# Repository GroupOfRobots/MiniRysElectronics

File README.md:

# RyśBoard Hardware Controller

This project involves the design and development of the RyśBoard hardware controller, a custom PCB created to manage a robotic system. The project aims to enhance the performance of the previous controller and involves various stages such as component selection, PCB manufacturing, and assembly. The documentation outlines the key sections of the controller, its power sources, communication interfaces, and overall production process.

## Table of Contents

1. [Key Sections of the Controller](#key-sections-of-the-controller)
   - [24V Power Supply](#24v-power-supply)
   - [5V Power Supply](#5v-power-supply)
   - [Motor Drivers](#motor-drivers)
   - [Battery Voltage Monitoring](#battery-voltage-monitoring)
   - [Battery Connectors](#battery-connectors)
   - [I/O Connectors](#io-connectors)
   - [Configurable Indicators](#configurable-indicators)
   - [Mounting Options](#mounting-options)
3. [Production Process](#production-process)
   - [Initial Project Design](#initial-project-design)
   - [Final Design in KiCad](#final-design-in-kicad)
   - [PCB Assembly](#pcb-assembly)

---

## Project Overview

This report summarizes the development of the RyśBoard hardware controller, which underwent several updates to improve its functionality. The work involved ordering components, manufacturing and assembling the PCBs, and evaluating the performance of the power supply systems.

---

## Key Sections of the Controller

### 24V Power Supply

The 24V power supply is based on the LM51231-Q1 chip and provides up to 2.5A, delivering max 60W of power. This ensures sufficient power for the stepper motors and their drivers, with a margin to accommodate future increases in power requirements.

### 5V Power Supply

A TPS565242-based 5V power supply provides up to 4A, delivering max 20W of power. It is designed to power the Raspberry Pi 4 and Raspberry Pi 5, allowing for smooth operation even with additional accessories such as fans.

### Motor Drivers

The motor drivers use L6470H chips, which meet the requirements of the stepper motors (drawing up to 1A per driver under full load). These drivers are essential for stabilizing motor control.

### Battery Voltage Monitoring

The MAX11613 ADC monitors the voltage of three batteries, each connected to a separate channel. This information is communicated to the control unit via an I²C bus, allowing real-time monitoring of battery status.

### Battery Connectors

Three battery connectors are currently used, but due to their large size, there may be a future revision to consolidate them into a single, more compact connector to optimize space on the PCB.

### I/O Connectors

The board includes dedicated connectors for each stepper motor, eight connectors for I²C sensors, and one connector each for SPI and UART devices. A 5V fan connector is also available for cooling.

### Configurable Indicators

The board is equipped with configurable LEDs (red and green) connected to GPIO pins 23 and 24 on the control unit. These can be used to signal different status conditions.

### Mounting Options

The controller is compatible with the Raspberry Pi HAT standard, allowing easy integration with Raspberry Pi systems. Care has been taken to ensure electrical insulation and secure mounting.

---

## Production Process

### Initial Project Design

The initial design phase involved five key tasks:
1. Designing the HAT-compliant add-on board for Raspberry Pi.
2. Proper placement of components for the 24V and 5V power supplies.
3. Ensuring effective heat dissipation for the motor drivers.
4. Positioning passive components for ADC and other peripherals.
5. Routing power and signal paths.

### Final Design in KiCad

The KiCad design process was iterative, focusing on:
- Component placement to ensure efficient routing.
- Optimizing power trace lengths and widths for lower heat generation and energy loss.
- Optimizing signal trace lengths and placement for lower crosstalk.
- Revising the transistor selection for the 24V power supply to improve efficiency and component availability.

Final modifications included changing the location of key components for better thermal management and adding identification markings for easier assembly.

### PCB Assembly

The assembly phase involved:
1. Ordering components primarily from Mouser Electronics.
2. Soldering the components onto the PCB.
3. Inspecting the board for any mechanical defects, such as excess solder or improper connections.

The PCB assembly required soldering both the top and bottom components, with careful attention to ensure proper connections and functionality.

---

## Project Status

- **Current version**: Final (PCB ver. 1.1)
- **Changes since last iteration**: Fixed problems with stability of internal voltage regulators of L6470H drivers

---

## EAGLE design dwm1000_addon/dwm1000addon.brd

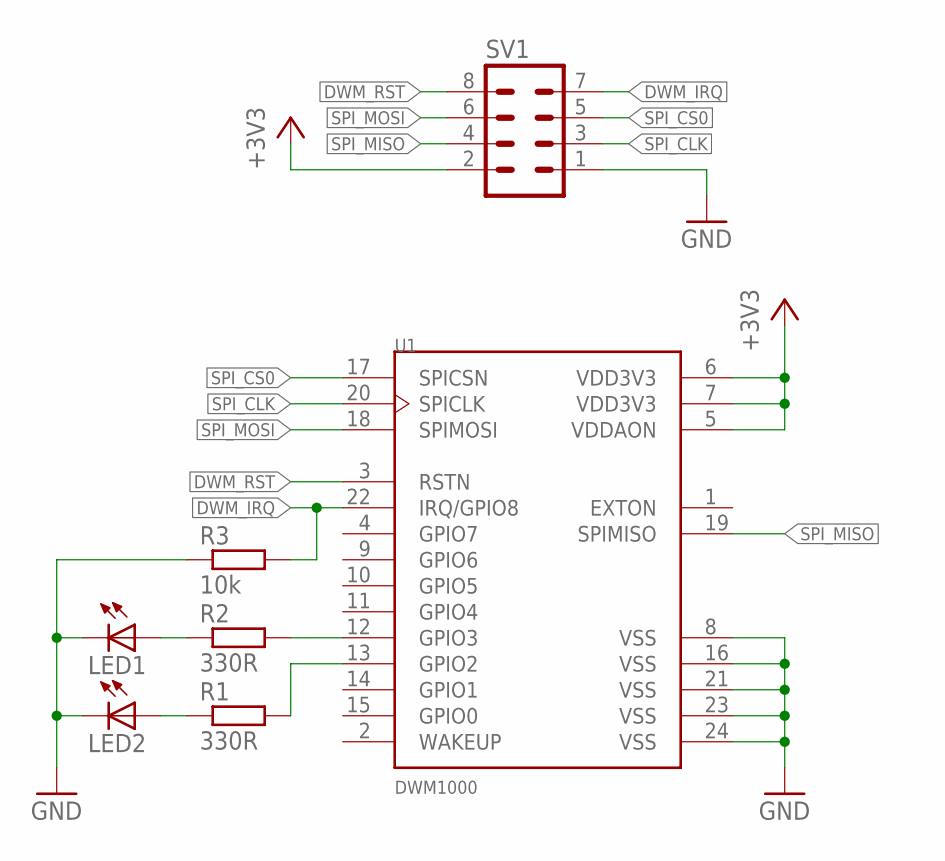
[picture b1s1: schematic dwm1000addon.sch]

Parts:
LED1, LED2: LEDCHIPLED_0603; CHIPLED_0603
R1, R2: 330R; R0603
R3: 10k; R0603
SV1: MA04-2
U1: DWM1000; XCVR_DWM1000

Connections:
+3V3: SV1.2, U1.5 (VDDAON), U1.6 (VDD3V3), U1.7 (VDD3V3)
DWM_IRQ: R3.2, SV1.7, U1.22 (IRQ/GPIO8)
DWM_RST: SV1.8, U1.3 (RSTN)
GND: LED1.C, LED2.C, R3.1, SV1.1, U1.8 (VSS), U1.16 (VSS), U1.21 (VSS), U1.23 (VSS), U1.24 (VSS)
unnamed: LED2.A, R1.1
unnamed: R1.2, U1.13 (GPIO2)
unnamed: R2.2, U1.12 (GPIO3)
unnamed: LED1.A, R2.1
SPI_CLK: SV1.3, U1.20 (SPICLK)
SPI_CS0: SV1.5, U1.17 (SPICSN)
SPI_MISO: SV1.4, U1.19 (SPIMISO)
SPI_MOSI: SV1.6, U1.18 (SPIMOSI)

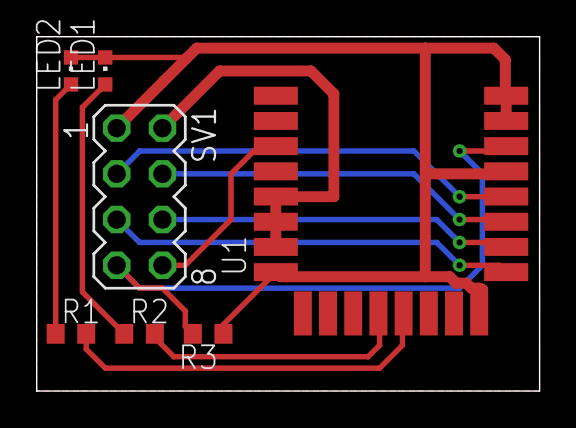
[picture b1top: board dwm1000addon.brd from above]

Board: 2 copper layers, 27.9 x 19.7 mm, 7 parts (0 on the bottom side), 12 nets.

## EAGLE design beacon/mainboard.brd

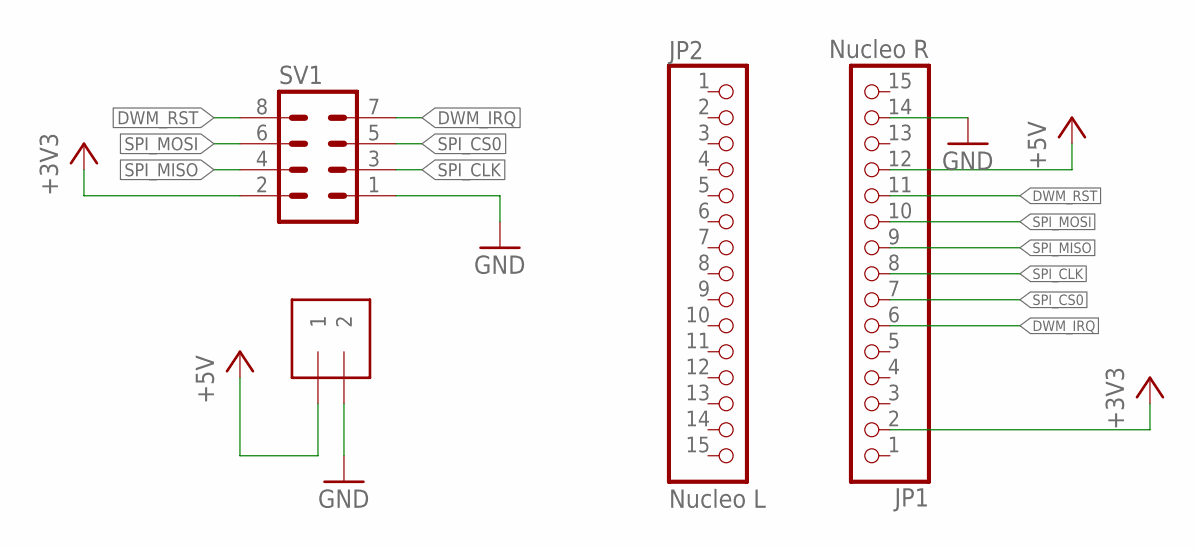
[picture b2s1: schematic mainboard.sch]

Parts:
J1: 1X2-3.5MM
JP1: Nucleo R; 1X15
JP2: Nucleo L; 1X15
SV1: MA04-2

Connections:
+3V3: JP1.2, SV1.2
+5V: J1.1, JP1.12
DWM_IRQ: JP1.6, SV1.7
DWM_RST: JP1.11, SV1.8
GND: J1.2, JP1.14, SV1.1
SPI_CLK: JP1.8, SV1.3
SPI_CS0: JP1.7, SV1.5
SPI_MISO: JP1.9, SV1.4
SPI_MOSI: JP1.10, SV1.6

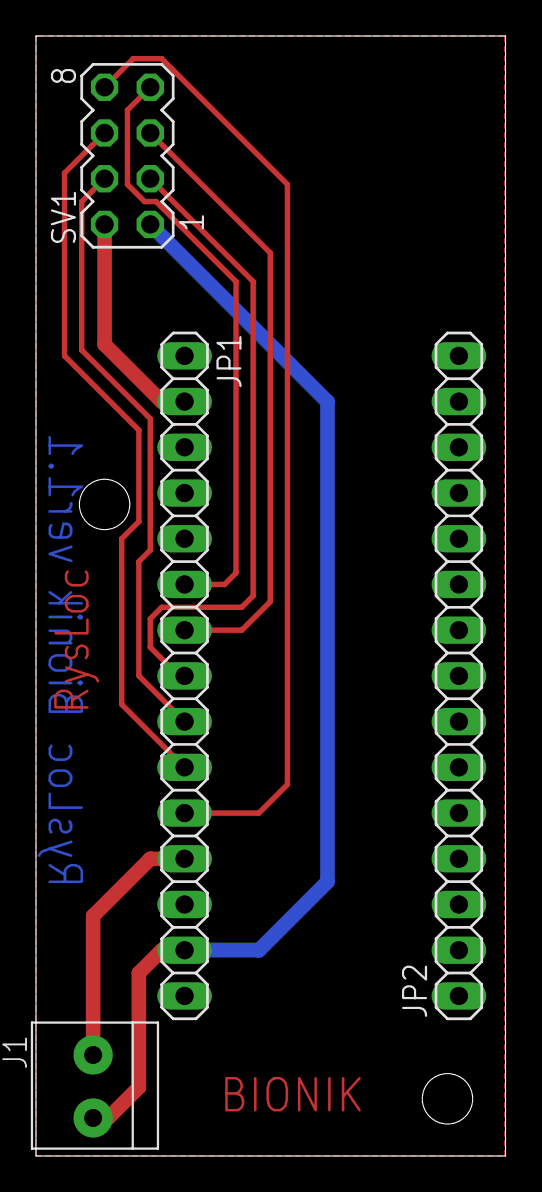
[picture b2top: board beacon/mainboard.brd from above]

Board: 2 copper layers, 26.1 x 62.2 mm, 4 parts (0 on the bottom side), 9 nets.

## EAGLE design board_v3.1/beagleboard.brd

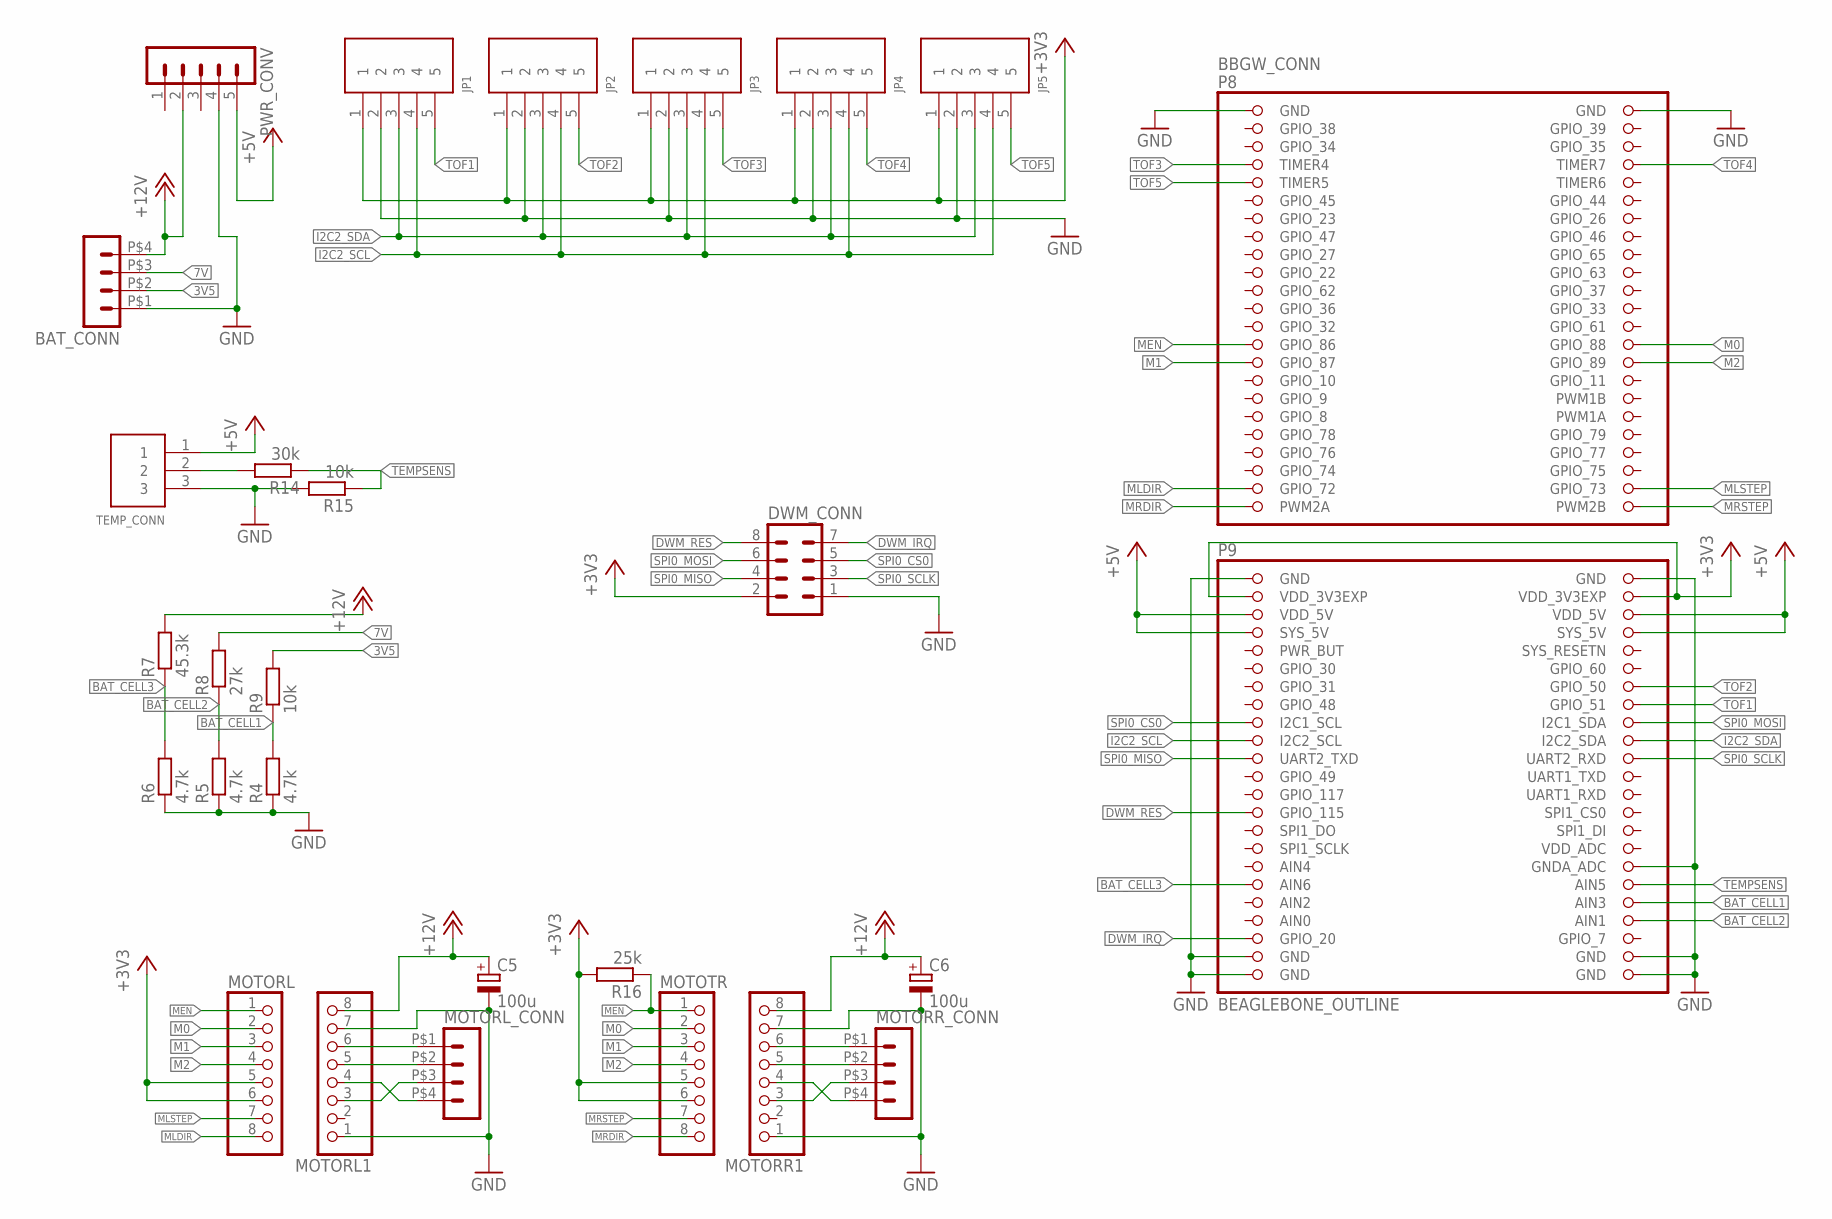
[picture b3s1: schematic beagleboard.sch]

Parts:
BAT_CONN: HEADER_POS4_43045-0412; 43045-0412
BBGW_CONN: BEAGLEBONE_OUTLINE; BEAGLEBONE_SHIELD
C5, C6: 100u; 153CLV-0405
DWM_CONN: MA04-2
JP1, JP2, JP3, JP4, JP5: 5PIN; B5B-PH-K-S
MOTORL, MOTORL1: PINHD-1X8; 1X08
MOTORL_CONN: HEADER_POS4_43045-0412; 43045-0412
MOTORR1: PINHD-1X8; 1X08
MOTORR_CONN: HEADER_POS4_43045-0412; 43045-0412
MOTOTR: PINHD-1X8; 1X08
PWR_CONV: MA05-1
R4, R5, R6: 4.7k; R0603
R7: 45.3k; R0603
R8: 27k; R0603
R9, R15: 10k; R0603
R14: 30k; R0603
R16: 25k; R0805
TEMP_CONN: 3PIN; B3B-PH-K-S

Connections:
3V5: BAT_CONN.P$2 (2), R9.2
7V: BAT_CONN.P$3 (3), R8.2
+3V3: BBGW_CONN.49 (VDD_3V3EXP), BBGW_CONN.50 (VDD_3V3EXP), DWM_CONN.2, JP1.1, JP2.1, JP3.1, JP4.1, JP5.1, MOTORL.5, MOTORL.6, MOTOTR.5, MOTOTR.6, R16.2
+5V: BBGW_CONN.51 (VDD_5V), BBGW_CONN.52 (VDD_5V), BBGW_CONN.53 (SYS_5V), BBGW_CONN.54 (SYS_5V), PWR_CONV.5, TEMP_CONN.1
+12V: BAT_CONN.P$4 (4), C5.+, C6.+, MOTORL1.8, MOTORR1.8, PWR_CONV.2, R7.2
AIN0: BBGW_CONN.85 (AIN0)
BAT_CELL1: BBGW_CONN.84 (AIN3), R4.2, R9.1
BAT_CELL2: BBGW_CONN.86 (AIN1), R5.2, R8.1
BAT_CELL3: BBGW_CONN.81 (AIN6), R6.2, R7.1
DWM_IRQ: BBGW_CONN.87 (GPIO_20), DWM_CONN.7
DWM_RES: BBGW_CONN.73 (GPIO_115), DWM_CONN.8
GND: BAT_CONN.P$1 (1), BBGW_CONN.1 (GND), BBGW_CONN.2 (GND), BBGW_CONN.47 (GND), BBGW_CONN.48 (GND), BBGW_CONN.80 (GNDA_ADC), BBGW_CONN.89 (GND), BBGW_CONN.90 (GND), BBGW_CONN.91 (GND), BBGW_CONN.92 (GND), C5.-, C6.-, DWM_CONN.1, JP1.2, JP2.2, JP3.2, JP4.2, JP5.2, MOTORL1.1, MOTORL1.7, MOTORR1.1, MOTORR1.7, PWR_CONV.4, R4.1, R5.1, R6.1, R15.2, TEMP_CONN.3
I2C2_SCL: BBGW_CONN.65 (I2C2_SCL), JP1.4, JP2.4, JP3.4, JP4.4, JP5.4
I2C2_SDA: BBGW_CONN.66 (I2C2_SDA), JP1.3, JP2.3, JP3.3, JP4.3, JP5.3
M0: BBGW_CONN.28 (GPIO_88), MOTORL.2, MOTOTR.2
M1: BBGW_CONN.29 (GPIO_87), MOTORL.3, MOTOTR.3
M2: BBGW_CONN.30 (GPIO_89), MOTORL.4, MOTOTR.4
MEN: BBGW_CONN.27 (GPIO_86), MOTORL.1, MOTOTR.1, R16.1
MLDIR: BBGW_CONN.43 (GPIO_72), MOTORL.8
MLSTEP: BBGW_CONN.44 (GPIO_73), MOTORL.7
MRDIR: BBGW_CONN.45 (PWM2A), MOTOTR.8
MRSTEP: BBGW_CONN.46 (PWM2B), MOTOTR.7
unnamed: MOTORL1.3, MOTORL_CONN.P$3 (3)
unnamed: MOTORL1.4, MOTORL_CONN.P$4 (4)
unnamed: MOTORR1.3, MOTORR_CONN.P$3 (3)
unnamed: MOTORR1.4, MOTORR_CONN.P$4 (4)
unnamed: MOTORL1.6, MOTORL_CONN.P$1 (1)
unnamed: MOTORL1.5, MOTORL_CONN.P$2 (2)
unnamed: MOTORR1.6, MOTORR_CONN.P$1 (1)
unnamed: MOTORR1.5, MOTORR_CONN.P$2 (2)
unnamed: R14.2, TEMP_CONN.2
SPI0_CS0: BBGW_CONN.63 (I2C1_SCL), DWM_CONN.5
SPI0_MISO: BBGW_CONN.67 (UART2_TXD), DWM_CONN.4
SPI0_MOSI: BBGW_CONN.64 (I2C1_SDA), DWM_CONN.6
SPI0_SCLK: BBGW_CONN.68 (UART2_RXD), DWM_CONN.3
TEMPSENS: BBGW_CONN.82 (AIN5), R14.1, R15.1
TOF1: BBGW_CONN.62 (GPIO_51), JP1.5
TOF2: BBGW_CONN.60 (GPIO_50), JP2.5
TOF3: BBGW_CONN.7 (TIMER4), JP3.5
TOF4: BBGW_CONN.8 (TIMER7), JP4.5
TOF5: BBGW_CONN.9 (TIMER5), JP5.5

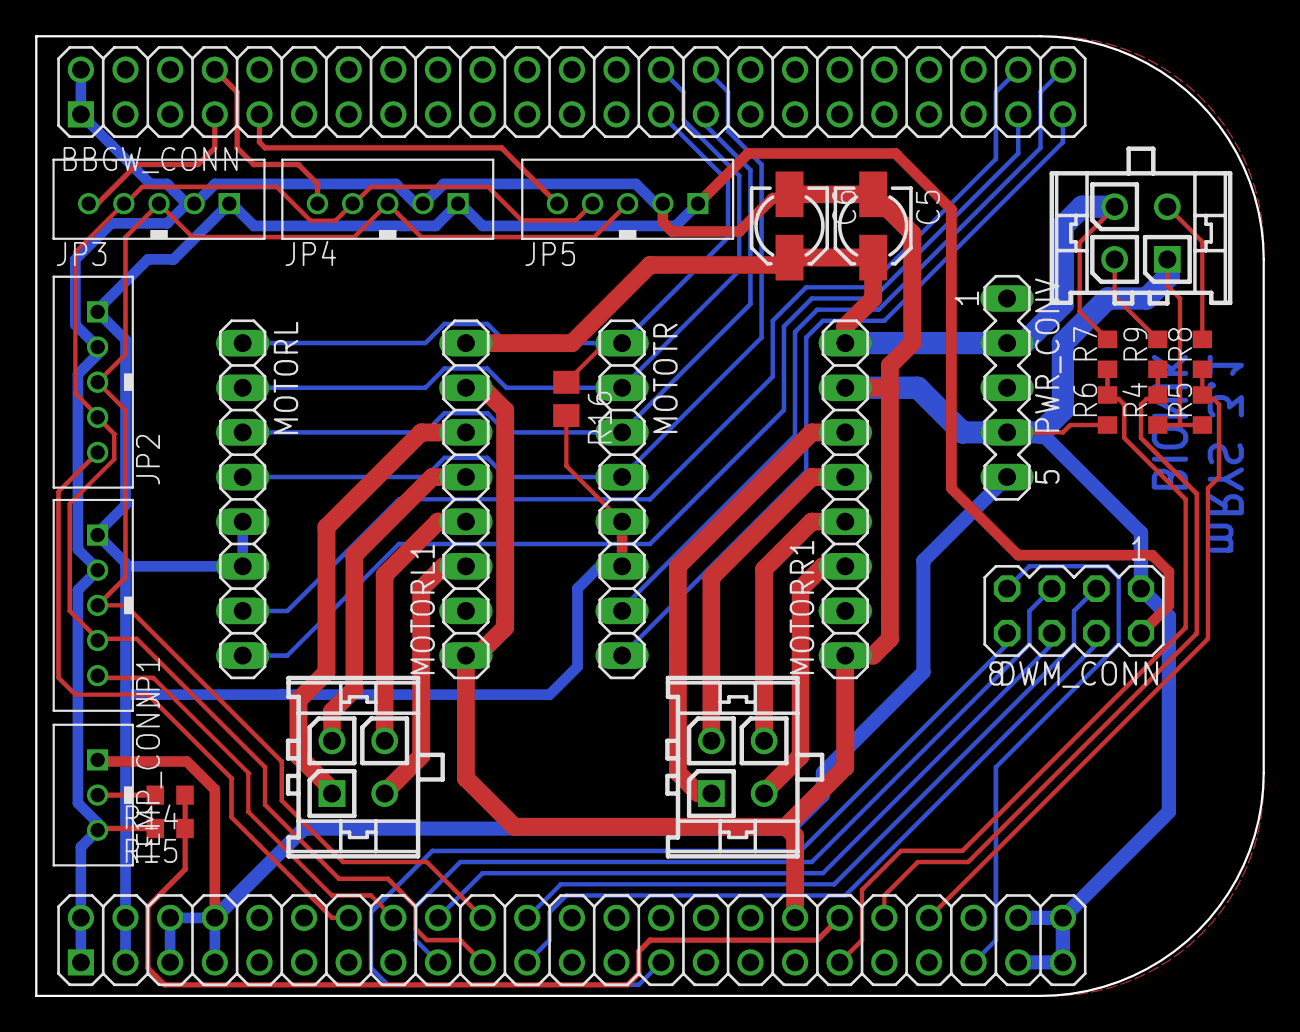
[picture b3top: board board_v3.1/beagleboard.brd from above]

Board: 2 copper layers, 69.8 x 54.6 mm, 27 parts (0 on the bottom side), 40 nets.

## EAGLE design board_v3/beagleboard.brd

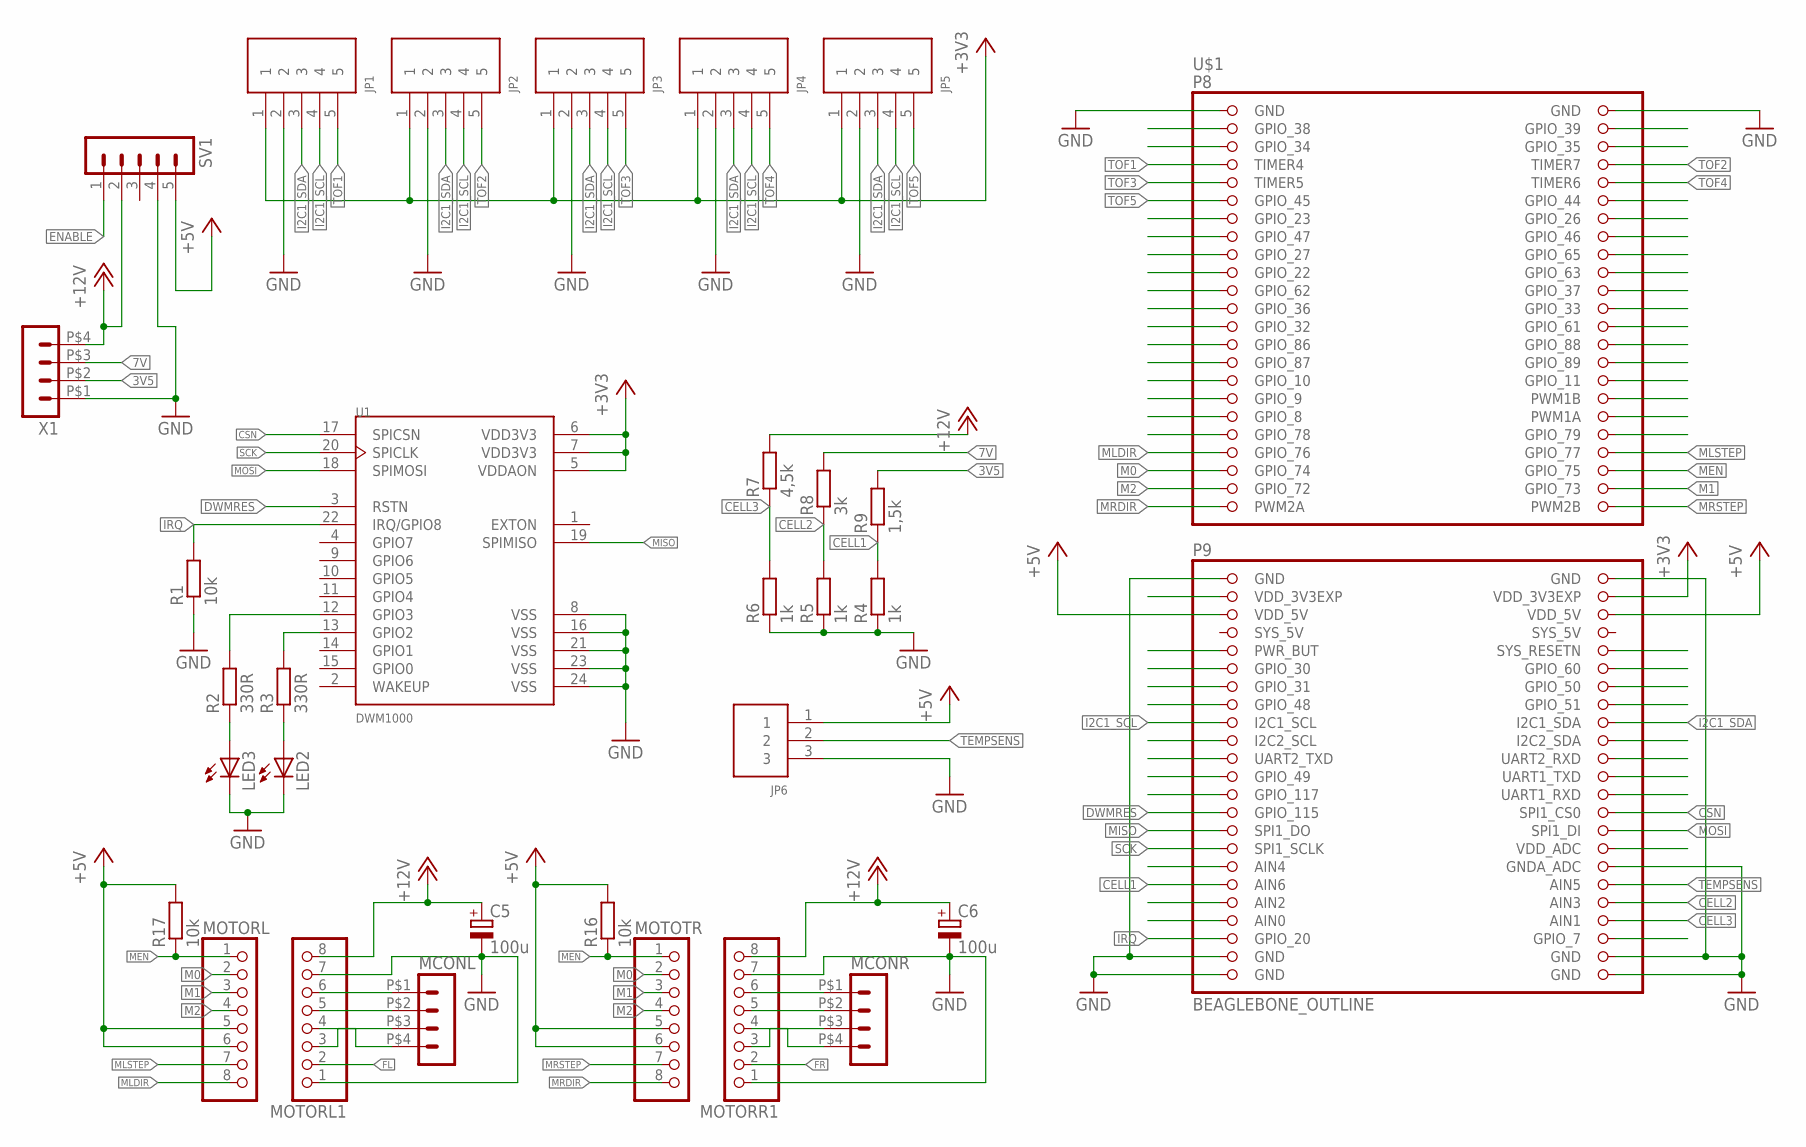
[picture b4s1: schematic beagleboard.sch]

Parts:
C5, C6: 100u; 153CLV-0405
JP1, JP2, JP3, JP4, JP5: 5PIN; B5B-PH-K-S
JP6: 3PIN; B3B-PH-K-S
LED2, LED3: LEDSML0603; SML0603
MCONL: HEADER_POS4_43045-0412; 43045-0412
MCONR: HEADER_POS4_43045-0412; 43045-0412
MOTORL, MOTORL1: PINHD-1X8; 1X08
MOTORR1: PINHD-1X8; 1X08
MOTOTR: PINHD-1X8; 1X08
R1: 10k; R0603
R2, R3: 330R; R0603
R4, R5, R6: 1k; R0603
R7: 4,5k; R0603
R8: 3k; R0603
R9: 1,5k; R0603
R16, R17: 10k; R0805
SV1: MA05-1
U1: DWM1000; XCVR_DWM1000
U$1: BEAGLEBONE_OUTLINE; BEAGLEBONE_SHIELD
X1: HEADER_POS4_43045-0412; 43045-0412

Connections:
3V5: R9.2, X1.P$2 (2)
7V: R8.2, X1.P$3 (3)
+3V3: JP1.1, JP2.1, JP3.1, JP4.1, JP5.1, U1.5 (VDDAON), U1.6 (VDD3V3), U1.7 (VDD3V3), U$1.50 (VDD_3V3EXP)
+5V: JP6.1, MOTORL.5, MOTORL.6, MOTOTR.5, MOTOTR.6, R16.2, R17.2, SV1.5, U$1.51 (VDD_5V), U$1.52 (VDD_5V)
+12V: C5.+, C6.+, MOTORL1.8, MOTORR1.8, R7.2, SV1.2, X1.P$4 (4)
CELL1: R4.2, R9.1, U$1.81 (AIN6)
CELL2: R5.2, R8.1, U$1.84 (AIN3)
CELL3: R6.2, R7.1, U$1.86 (AIN1)
CSN: U1.17 (SPICSN), U$1.74 (SPI1_CS0)
D4ECHO: U$1.85 (AIN0)
D4TRIG: U$1.83 (AIN2)
DWMRES: U1.3 (RSTN), U$1.73 (GPIO_115)
ENABLE: SV1.1
FL: MOTORL1.2
FR: MOTORR1.2
GND: C5.-, C6.-, JP1.2, JP2.2, JP3.2, JP4.2, JP5.2, JP6.3, LED2.C, LED3.C, MOTORL1.1, MOTORL1.7, MOTORR1.1, MOTORR1.7, R1.1, R4.1, R5.1, R6.1, SV1.4, U1.8 (VSS), U1.16 (VSS), U1.21 (VSS), U1.23 (VSS), U1.24 (VSS), U$1.1 (GND), U$1.2 (GND), U$1.47 (GND), U$1.80 (GNDA_ADC), U$1.89 (GND), U$1.90 (GND), U$1.91 (GND), U$1.92 (GND), X1.P$1 (1)
I2C1_SCL: JP1.4, JP2.4, JP3.4, JP4.4, JP5.4, U$1.63 (I2C1_SCL)
I2C1_SDA: JP1.3, JP2.3, JP3.3, JP4.3, JP5.3, U$1.64 (I2C1_SDA)
IRQ: R1.2, U1.22 (IRQ/GPIO8), U$1.87 (GPIO_20)
M0: MOTORL.2, MOTOTR.2, U$1.41 (GPIO_74)
M1: MOTORL.3, MOTOTR.3, U$1.44 (GPIO_73)
M2: MOTORL.4, MOTOTR.4, U$1.43 (GPIO_72)
MEN: MOTORL.1, MOTOTR.1, R16.1, R17.1, U$1.42 (GPIO_75)
MISO: U1.19 (SPIMISO), U$1.75 (SPI1_DO)
MLDIR: MOTORL.8, U$1.39 (GPIO_76)
MLSTEP: MOTORL.7, U$1.40 (GPIO_77)
MOSI: U1.18 (SPIMOSI), U$1.76 (SPI1_DI)
MRDIR: MOTOTR.8, U$1.45 (PWM2A)
MRSTEP: MOTOTR.7, U$1.46 (PWM2B)
unnamed: MCONL.P$4 (4), MOTORL1.4
unnamed: R3.2, U1.13 (GPIO2)
unnamed: R2.2, U1.12 (GPIO3)
unnamed: LED2.A, R3.1
unnamed: LED3.A, R2.1
unnamed: MCONL.P$1 (1), MOTORL1.6
unnamed: MCONL.P$2 (2), MOTORL1.5
unnamed: MCONL.P$3 (3), MOTORL1.3
unnamed: MCONR.P$1 (1), MOTORR1.6
unnamed: MCONR.P$2 (2), MOTORR1.5
unnamed: MCONR.P$4 (4), MOTORR1.4
unnamed: MCONR.P$3 (3), MOTORR1.3
SCK: U1.20 (SPICLK), U$1.77 (SPI1_SCLK)
SYS_5V: U$1.53 (SYS_5V)
TEMPSENS: JP6.2, U$1.82 (AIN5)
TOF1: JP1.5, U$1.7 (TIMER4)
TOF2: JP2.5, U$1.8 (TIMER7)
TOF3: JP3.5, U$1.9 (TIMER5)
TOF4: JP4.5, U$1.10 (TIMER6)
TOF5: JP5.5, U$1.11 (GPIO_45)

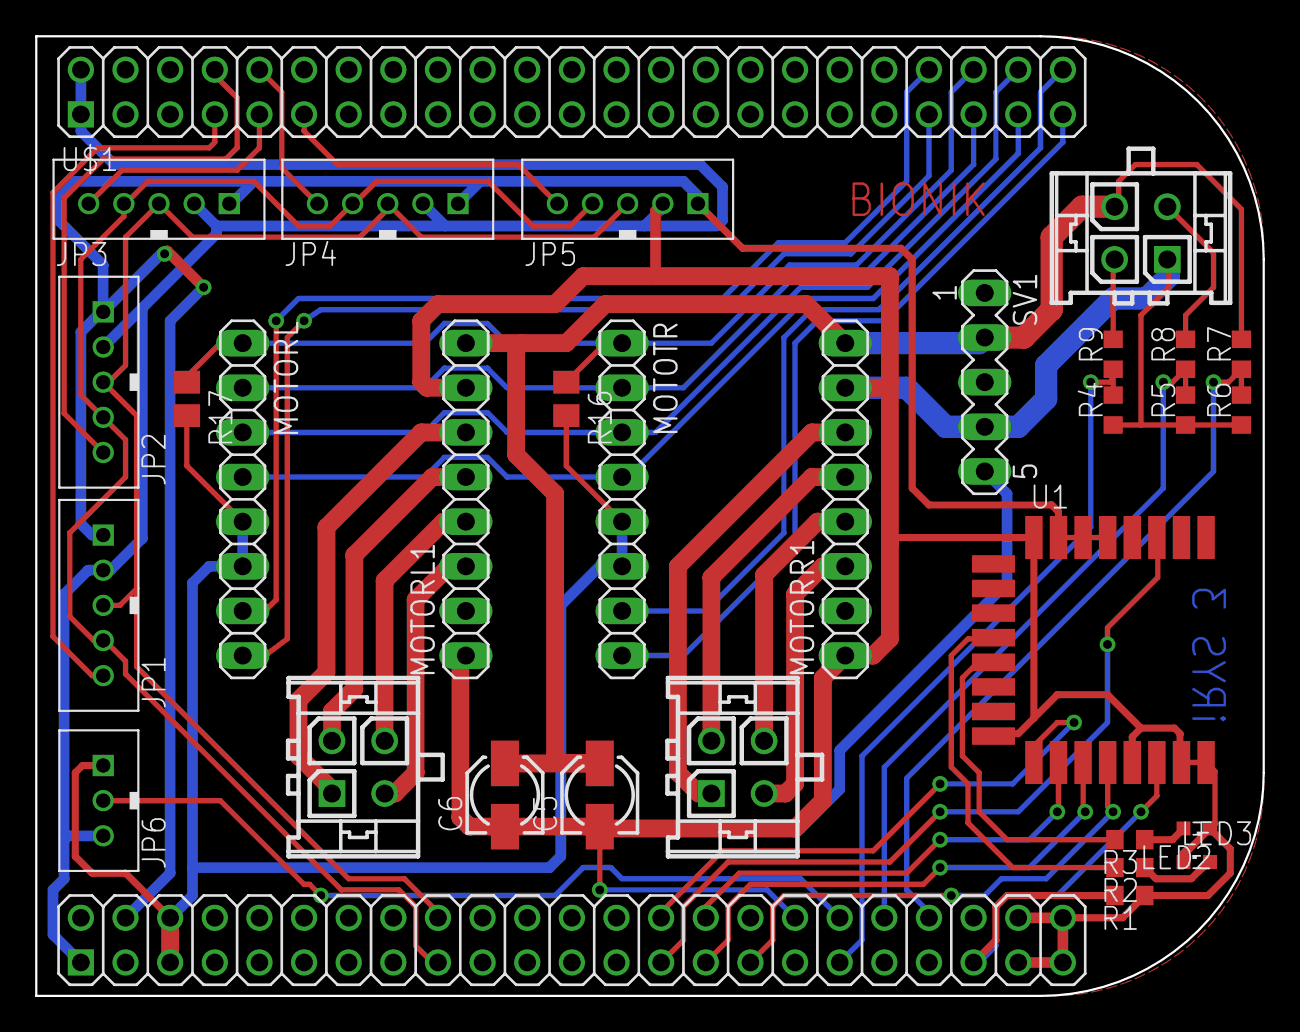
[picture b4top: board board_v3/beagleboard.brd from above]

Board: 2 copper layers, 69.8 x 54.6 mm, 31 parts (0 on the bottom side), 43 nets.

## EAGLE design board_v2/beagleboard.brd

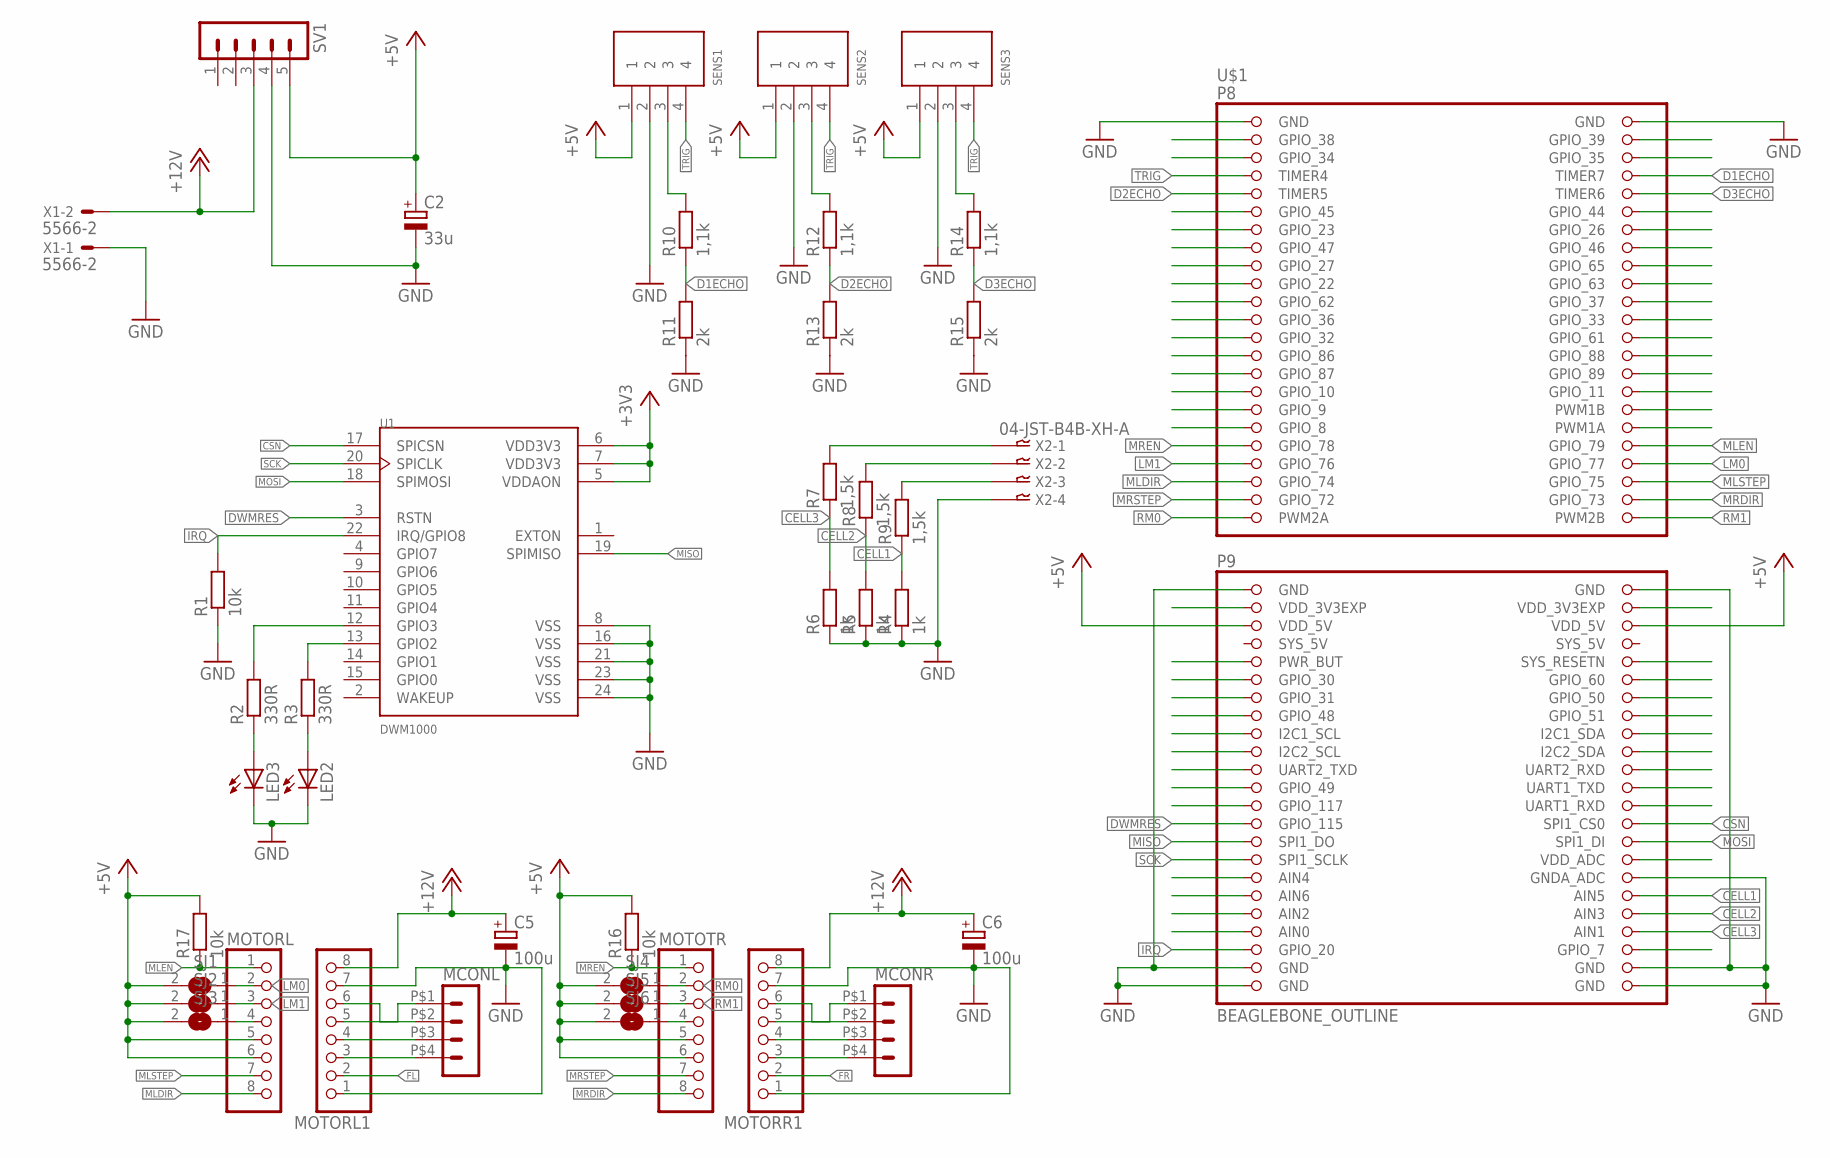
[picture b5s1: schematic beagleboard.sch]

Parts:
C2: 33u; 153CLV-0405
C5, C6: 100u; 153CLV-0405
LED2, LED3: LEDSML0603; SML0603
MCONL: HEADER_POS4_43045-0412; 43045-0412
MCONR: HEADER_POS4_43045-0412; 43045-0412
MOTORL, MOTORL1: PINHD-1X8; 1X08
MOTORR1: PINHD-1X8; 1X08
MOTOTR: PINHD-1X8; 1X08
R1: 10k; R0603
R2, R3: 330R; R0603
R4, R5, R6: 1k; R0805
R7, R8, R9: 1,5k; R0805
R10, R12, R14: 1,1k; R0805
R11, R13, R15: 2k; R0805
R16, R17: 10k; R0805
SENS1, SENS2, SENS3: 4PIN; B4B-PH-K-S
SJ1, SJ2, SJ3, SJ4, SJ5, SJ6: SJ
SV1: MA05-1
U1: DWM1000; XCVR_DWM1000
U$1: BEAGLEBONE_OUTLINE; BEAGLEBONE_SHIELD
X1: 5566-2
X2: 04-JST-B4B-XH-A; B4B-XH

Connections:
+3V3: U1.5 (VDDAON), U1.6 (VDD3V3), U1.7 (VDD3V3)
+5V: C2.+, MOTORL.5, MOTORL.6, MOTOTR.5, MOTOTR.6, R16.2, R17.2, SENS1.1, SENS2.1, SENS3.1, SJ1.2, SJ2.2, SJ3.2, SJ4.2, SJ5.2, SJ6.2, SV1.5, U$1.51 (VDD_5V), U$1.52 (VDD_5V)
+12V: C5.+, C6.+, MOTORL1.8, MOTORR1.8, SV1.3, X1.2
CELL1: R4.2, R9.1, U$1.82 (AIN5)
CELL2: R5.2, R8.1, U$1.84 (AIN3)
CELL3: R6.2, R7.1, U$1.86 (AIN1)
CSN: U1.17 (SPICSN), U$1.74 (SPI1_CS0)
D1ECHO: R10.1, R11.2, U$1.8 (TIMER7)
D2ECHO: R12.1, R13.2, U$1.9 (TIMER5)
D3ECHO: R14.1, R15.2, U$1.10 (TIMER6)
D4ECHO: U$1.85 (AIN0)
D4TRIG: U$1.83 (AIN2)
DWMRES: U1.3 (RSTN), U$1.73 (GPIO_115)
FL: MOTORL1.2
FR: MOTORR1.2
GND: C2.-, C5.-, C6.-, LED2.C, LED3.C, MOTORL1.1, MOTORL1.7, MOTORR1.1, MOTORR1.7, R1.1, R4.1, R5.1, R6.1, R11.1, R13.1, R15.1, SENS1.2, SENS2.2, SENS3.2, SV1.4, U1.8 (VSS), U1.16 (VSS), U1.21 (VSS), U1.23 (VSS), U1.24 (VSS), U$1.1 (GND), U$1.2 (GND), U$1.47 (GND), U$1.80 (GNDA_ADC), U$1.89 (GND), U$1.90 (GND), U$1.91 (GND), U$1.92 (GND), X1.1, X2.P$4
IRQ: R1.2, U1.22 (IRQ/GPIO8), U$1.87 (GPIO_20)
LM0: MOTORL.2, SJ1.1, U$1.40 (GPIO_77)
LM1: MOTORL.3, SJ2.1, U$1.39 (GPIO_76)
MISO: U1.19 (SPIMISO), U$1.75 (SPI1_DO)
MLDIR: MOTORL.8, U$1.41 (GPIO_74)
MLEN: MOTORL.1, R17.1, U$1.38 (GPIO_79)
MLSTEP: MOTORL.7, U$1.42 (GPIO_75)
MOSI: U1.18 (SPIMOSI), U$1.76 (SPI1_DI)
MRDIR: MOTOTR.8, U$1.44 (GPIO_73)
MREN: MOTOTR.1, R16.1, U$1.37 (GPIO_78)
MRSTEP: MOTOTR.7, U$1.43 (GPIO_72)
unnamed: MCONL.P$3 (3), MOTORL1.4
unnamed: R3.2, U1.13 (GPIO2)
unnamed: R2.2, U1.12 (GPIO3)
unnamed: R7.2, X2.P$1
unnamed: LED2.A, R3.1
unnamed: LED3.A, R2.1
unnamed: R8.2, X2.P$2
unnamed: R9.2, X2.P$3
unnamed: MCONL.P$2 (2), MOTORL1.6
unnamed: MCONL.P$1 (1), MOTORL1.5
unnamed: MCONL.P$4 (4), MOTORL1.3
unnamed: MCONR.P$2 (2), MOTORR1.6
unnamed: MCONR.P$3 (3), MOTORR1.4
unnamed: MCONR.P$4 (4), MOTORR1.3
unnamed: MCONR.P$1 (1), MOTORR1.5
unnamed: MOTORL.4, SJ3.1
unnamed: MOTOTR.4, SJ6.1
unnamed: R10.2, SENS1.3
unnamed: R12.2, SENS2.3
unnamed: R14.2, SENS3.3
RM0: MOTOTR.2, SJ4.1, U$1.45 (PWM2A)
RM1: MOTOTR.3, SJ5.1, U$1.46 (PWM2B)
SCK: U1.20 (SPICLK), U$1.77 (SPI1_SCLK)
SYS_5V: U$1.53 (SYS_5V)
TRIG: SENS1.4, SENS2.4, SENS3.4, U$1.7 (TIMER4)

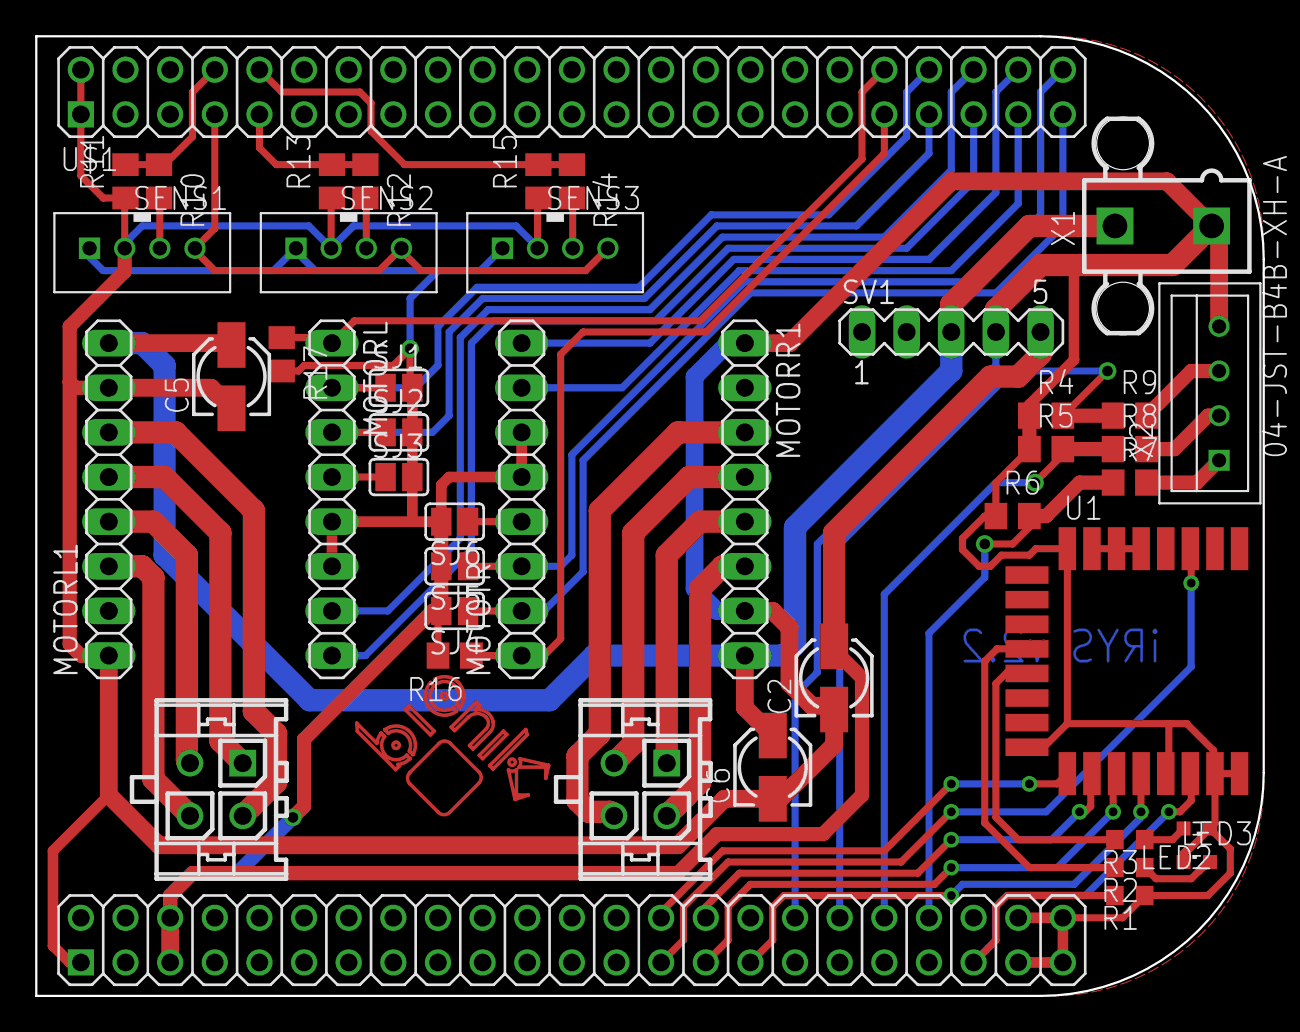
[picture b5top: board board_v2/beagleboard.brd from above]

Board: 2 copper layers, 69.8 x 54.6 mm, 42 parts (0 on the bottom side), 47 nets.

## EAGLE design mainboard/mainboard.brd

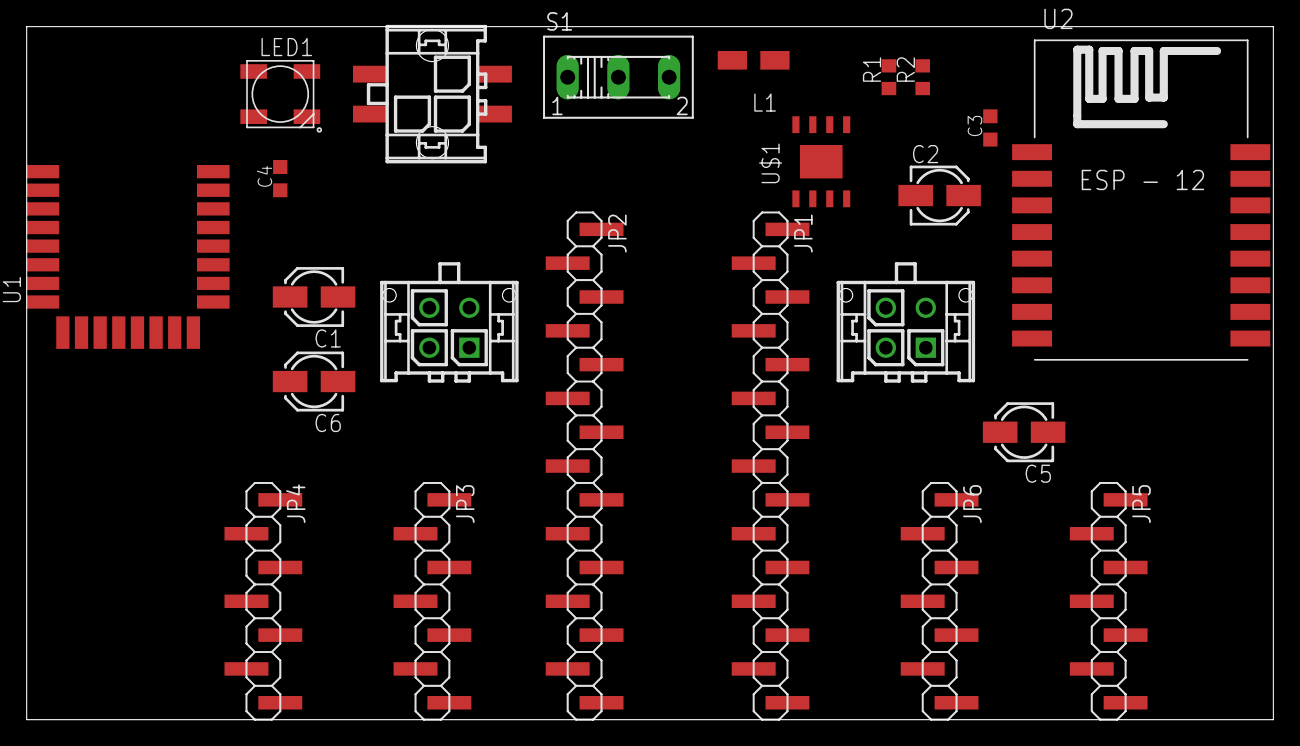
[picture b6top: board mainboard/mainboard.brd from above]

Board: 2 copper layers, 93.7 x 52.1 mm, 23 parts (0 on the bottom side), 9 nets, no tracks yet.

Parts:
C1, C2, C5, C6: 153CLV-0405
C3, C4: C0603K
JP1: Nucleo R; 1X15SMD
JP2: Nucleo L; 1X15SMD
JP3: Motor LR; 1X07SMD
JP4: Motor LL; 1X07SMD
JP5: Motor RL; 1X07SMD
JP6: Motor RR; 1X07SMD
L1: L4035M
LED1: WS2812B
R1, R2: R0603
S1: 255SB
U1: DWM1000; XCVR_DWM1000
U2: ESP8266; ESP12-SMD
U$1: ST1S10PHR; HSOP8
X1, X2: 43045-0412
X3: 43045-0415

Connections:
+5V: C2.+, L1.2, R1.2
+12V: S1.2, X3.P$3, X3.P$4
GND: C1.-, C2.-, C3.2, C5.-, C6.-, R2.1, U$1.4, U$1.5, U$1.8, U$1.9, X3.P$1, X3.P$2
unnamed: L1.1, U$1.7
unnamed: R1.1, R2.2, U$1.3
unnamed: C1.+, C3.1, S1.1, U$1.1, U$1.2, U$1.6
unnamed: C4.1, LED1.VSS
VDD3V3: U1.6, U1.7
VSS: U1.8, U1.16, U1.21, U1.23, U1.24

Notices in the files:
parts and their libraries:
SparkFun-Connectors: Licensing: Creative Commons ShareAlike 4.0 International - https://creativecommons.org/licenses/by-sa/4.0
